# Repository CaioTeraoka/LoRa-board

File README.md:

# LoRa-board
This project is a development board that was made with the purpose of being used to create and test simples projects that contains LoRaWAN communication. Besides the LoRaWAN usage, this board also has CAN bus communication and a sensor of temperature and humidity to expand the board possibilities.

## Specifications:
**LoRa Frequency** - Only 915MHz <br>
**Power** - 5V using the USB Micro <br>
**Stackup:**
1. Signal + Components
2. Ground
3. Power
4. Ground + Components

## Main Components
- STM32F103 <br>
The STM32F103 is a series of microcontrollers developed by STMicroelectronics. It's part of the STM32 family of microcontrollers, which are based on the ARM Cortex-M processor architecture. 

- LX1276 <br>
The SX1276 is a widely known RF (Radio Frequency) transceiver module. It is a product from Semtech, a semiconductor company that specializes in wireless communication solutions. The SX1276 is part of the Semtech's LoRa (Long Range) technology family.

- SN65HVD230 <br>
The SN65HVD230 is a popular transceiver chip designed for use in Controller Area Network (CAN) bus communication systems. CAN is a widely used network protocol in automotive and industrial applications for communication between various electronic control units (ECUs) or devices. 

- AHT20 <br>
The AHT20 is a digital humidity and temperature sensor manufactured by ASAIR, a company specializing in environmental sensing solutions. The AHT20 sensor is designed to accurately measure both humidity and temperature in various applications.

## 3D Model

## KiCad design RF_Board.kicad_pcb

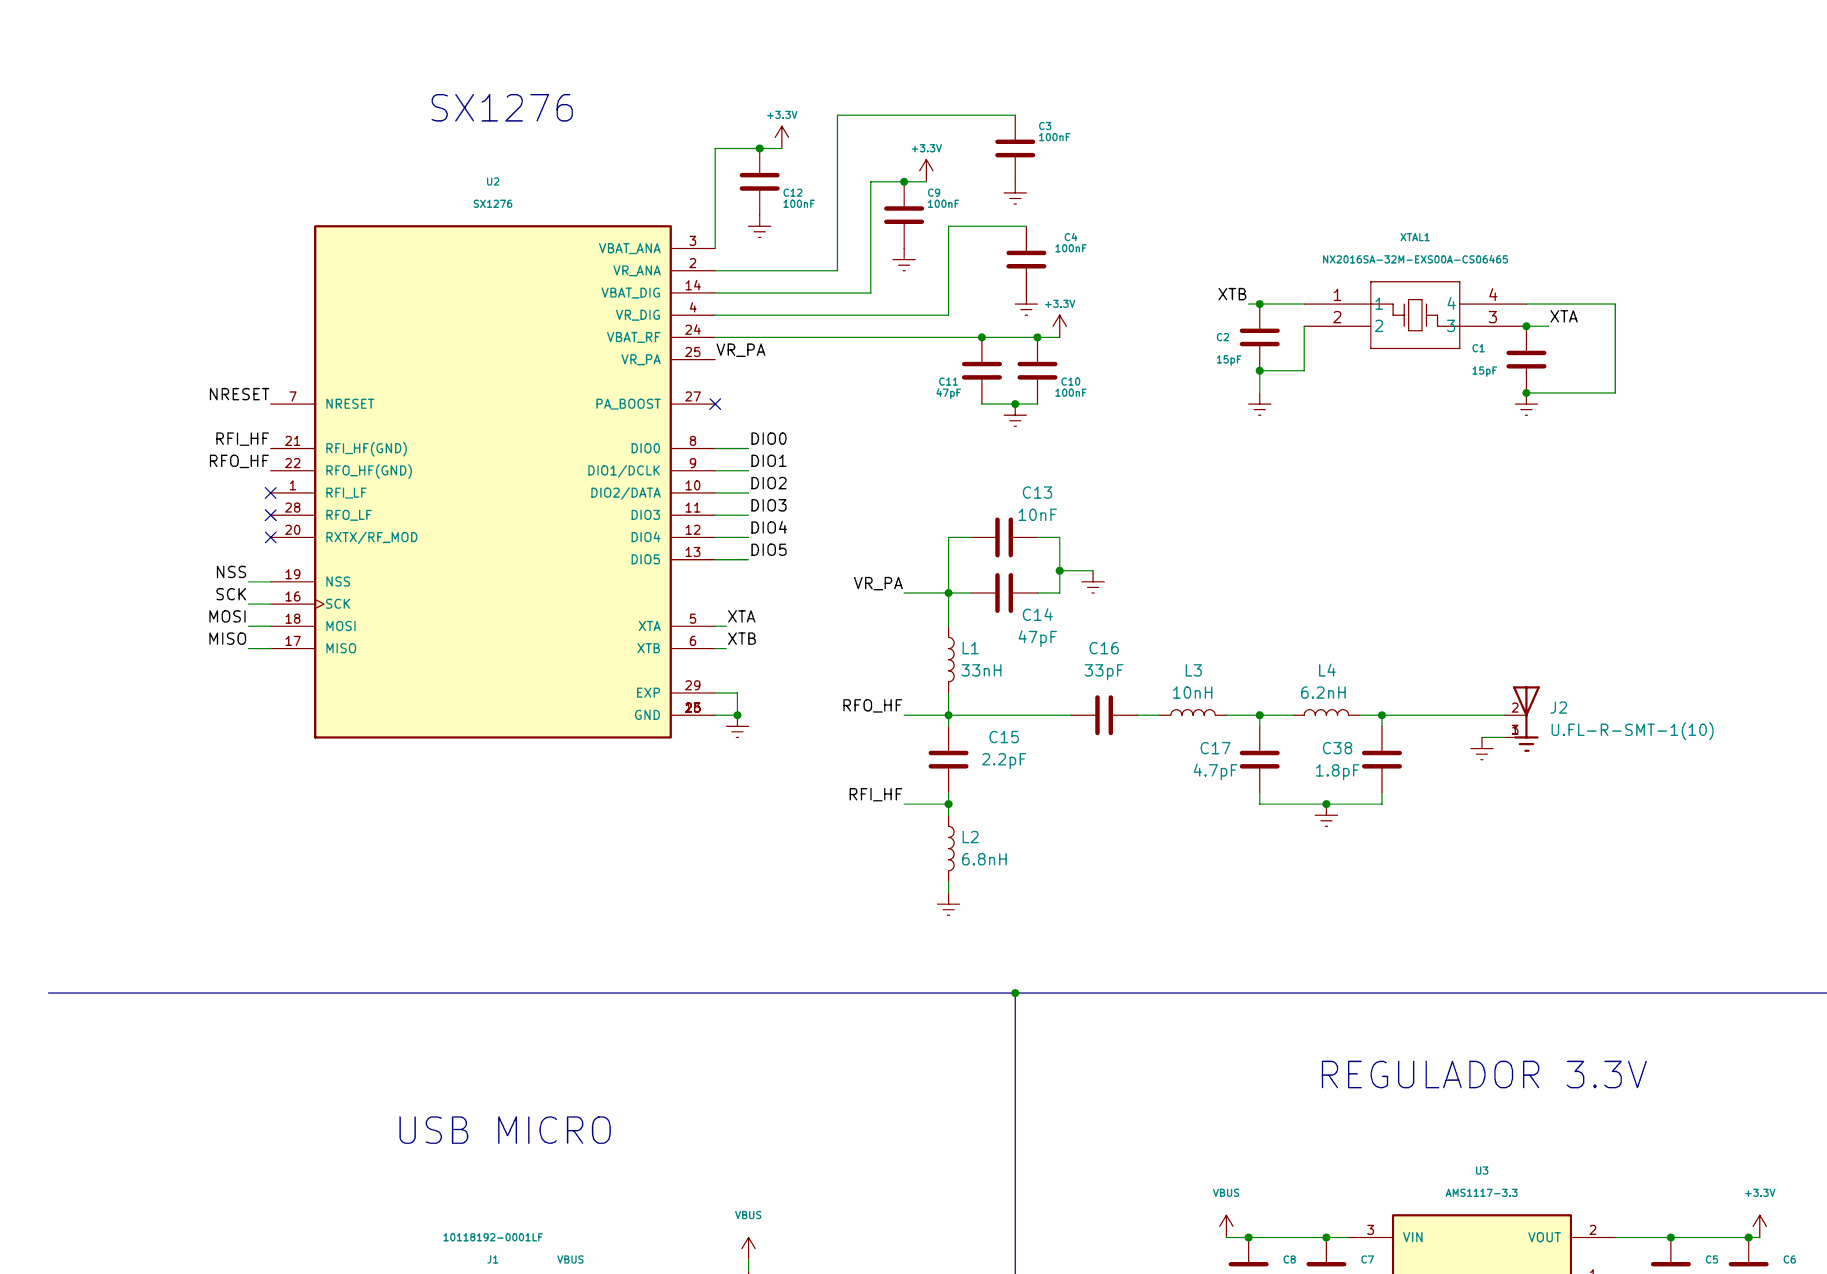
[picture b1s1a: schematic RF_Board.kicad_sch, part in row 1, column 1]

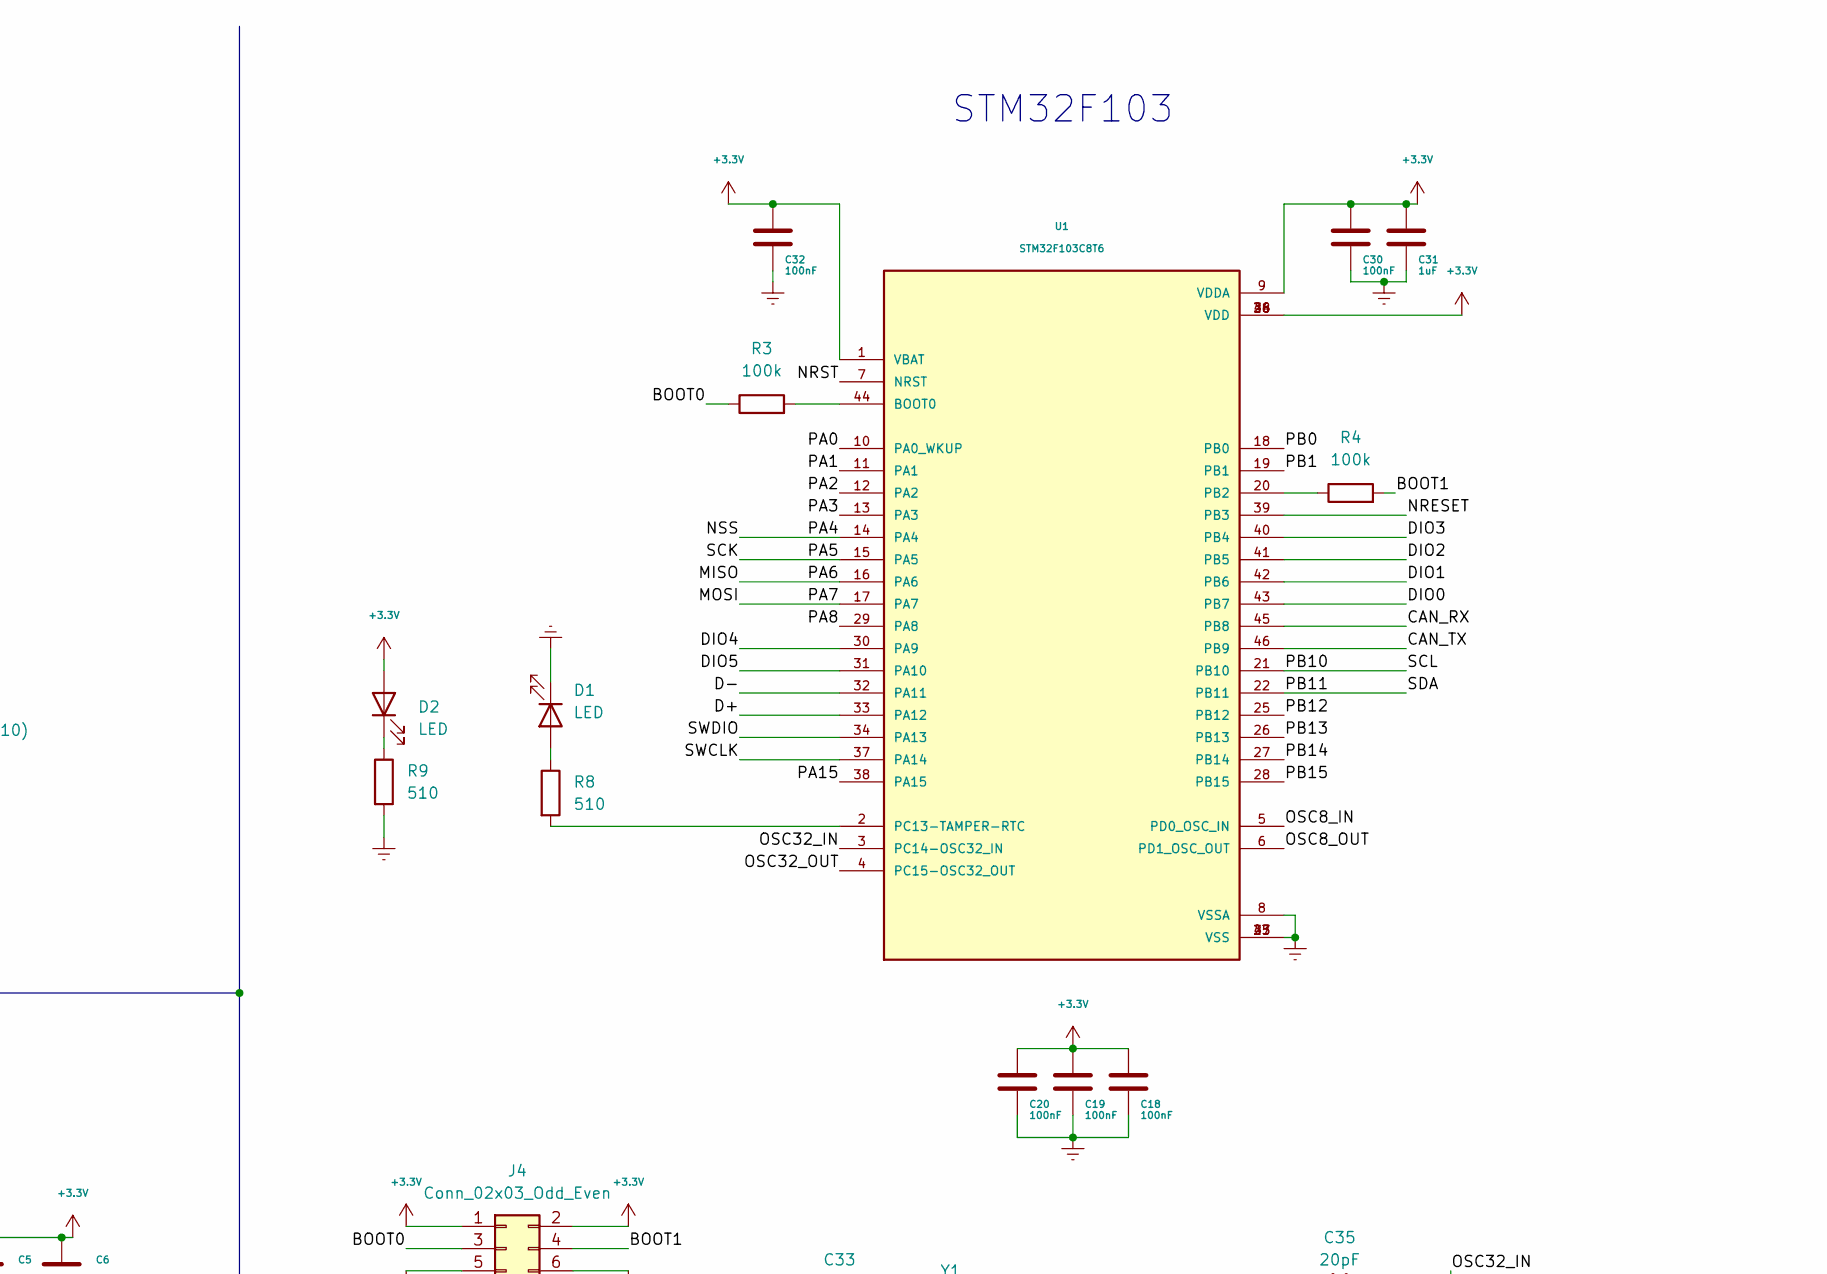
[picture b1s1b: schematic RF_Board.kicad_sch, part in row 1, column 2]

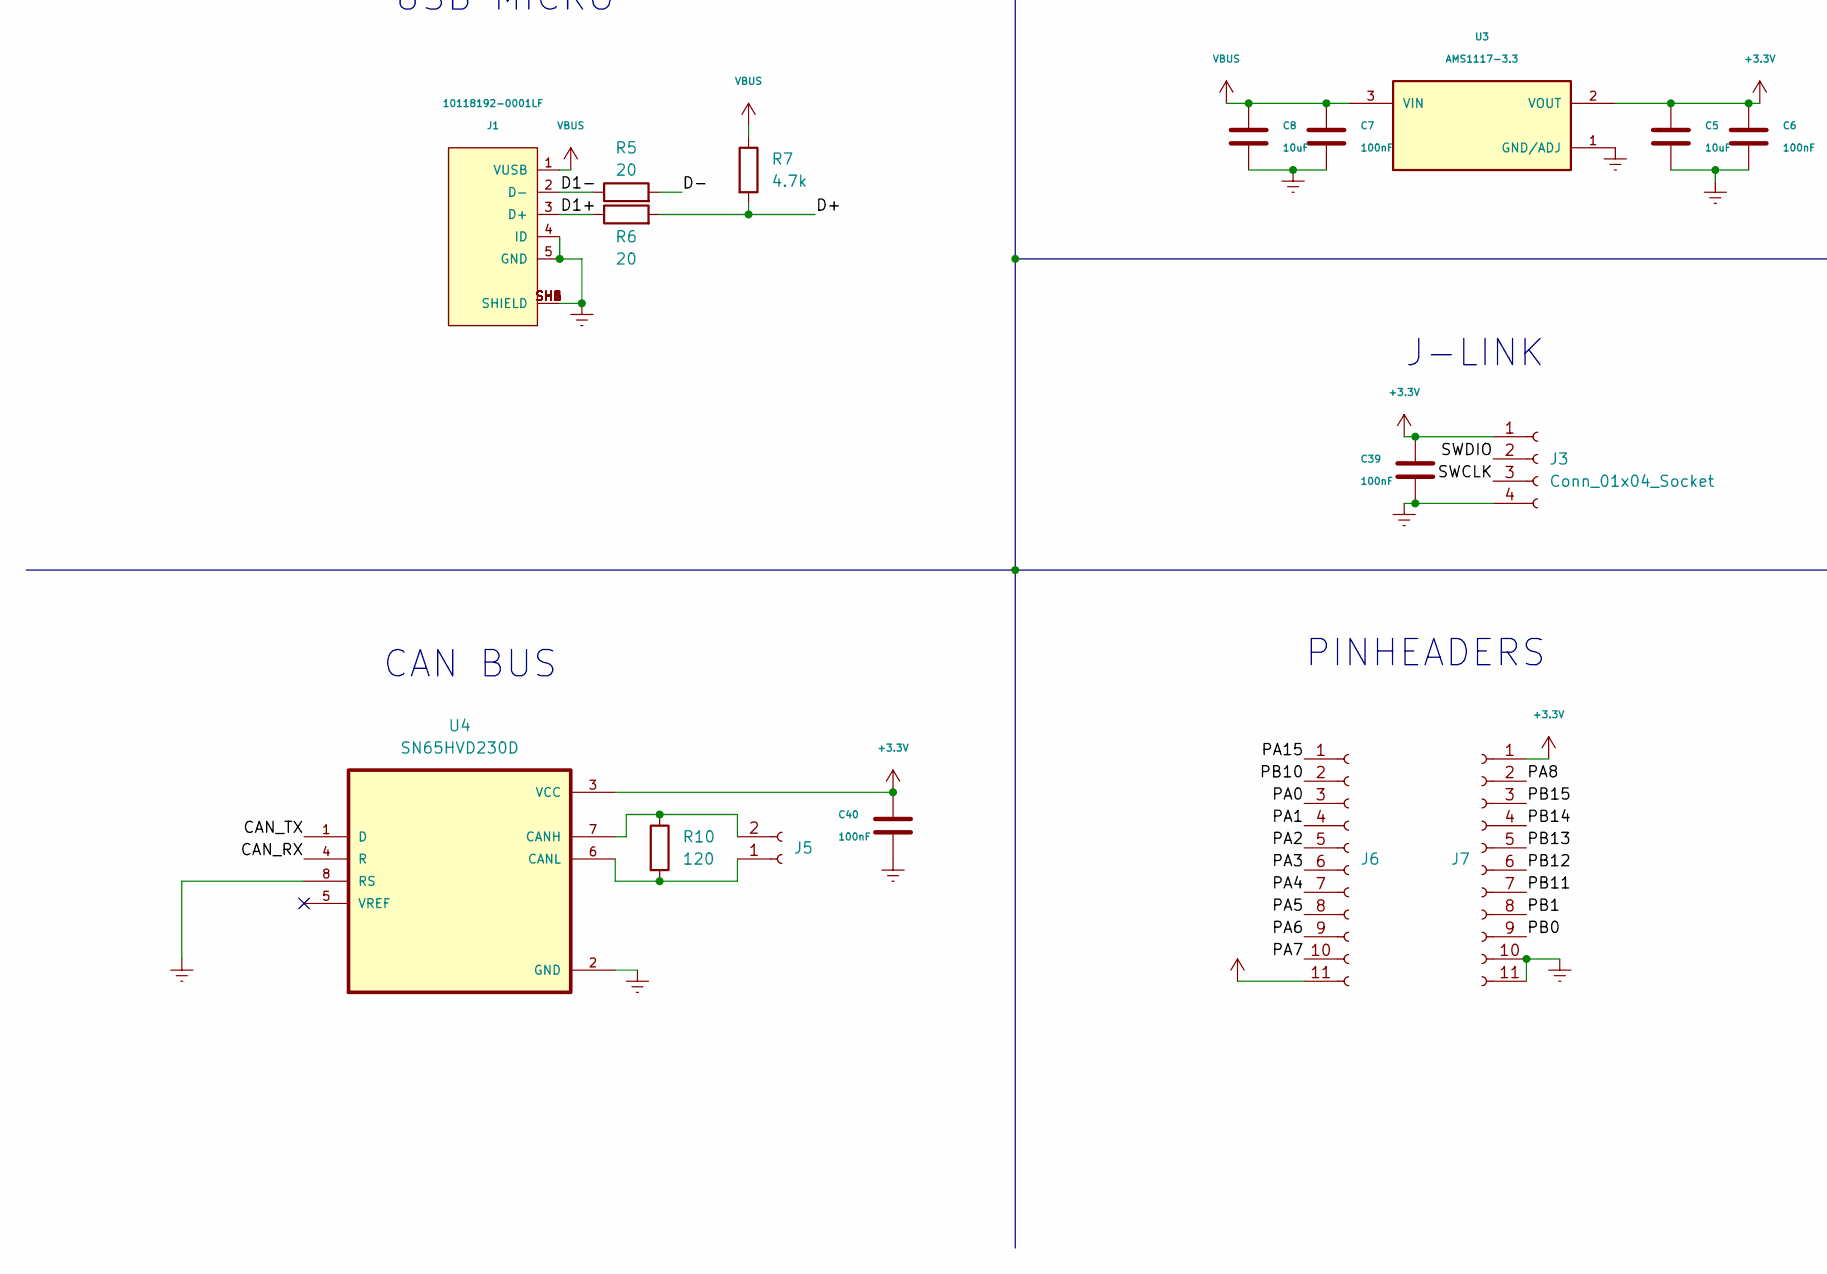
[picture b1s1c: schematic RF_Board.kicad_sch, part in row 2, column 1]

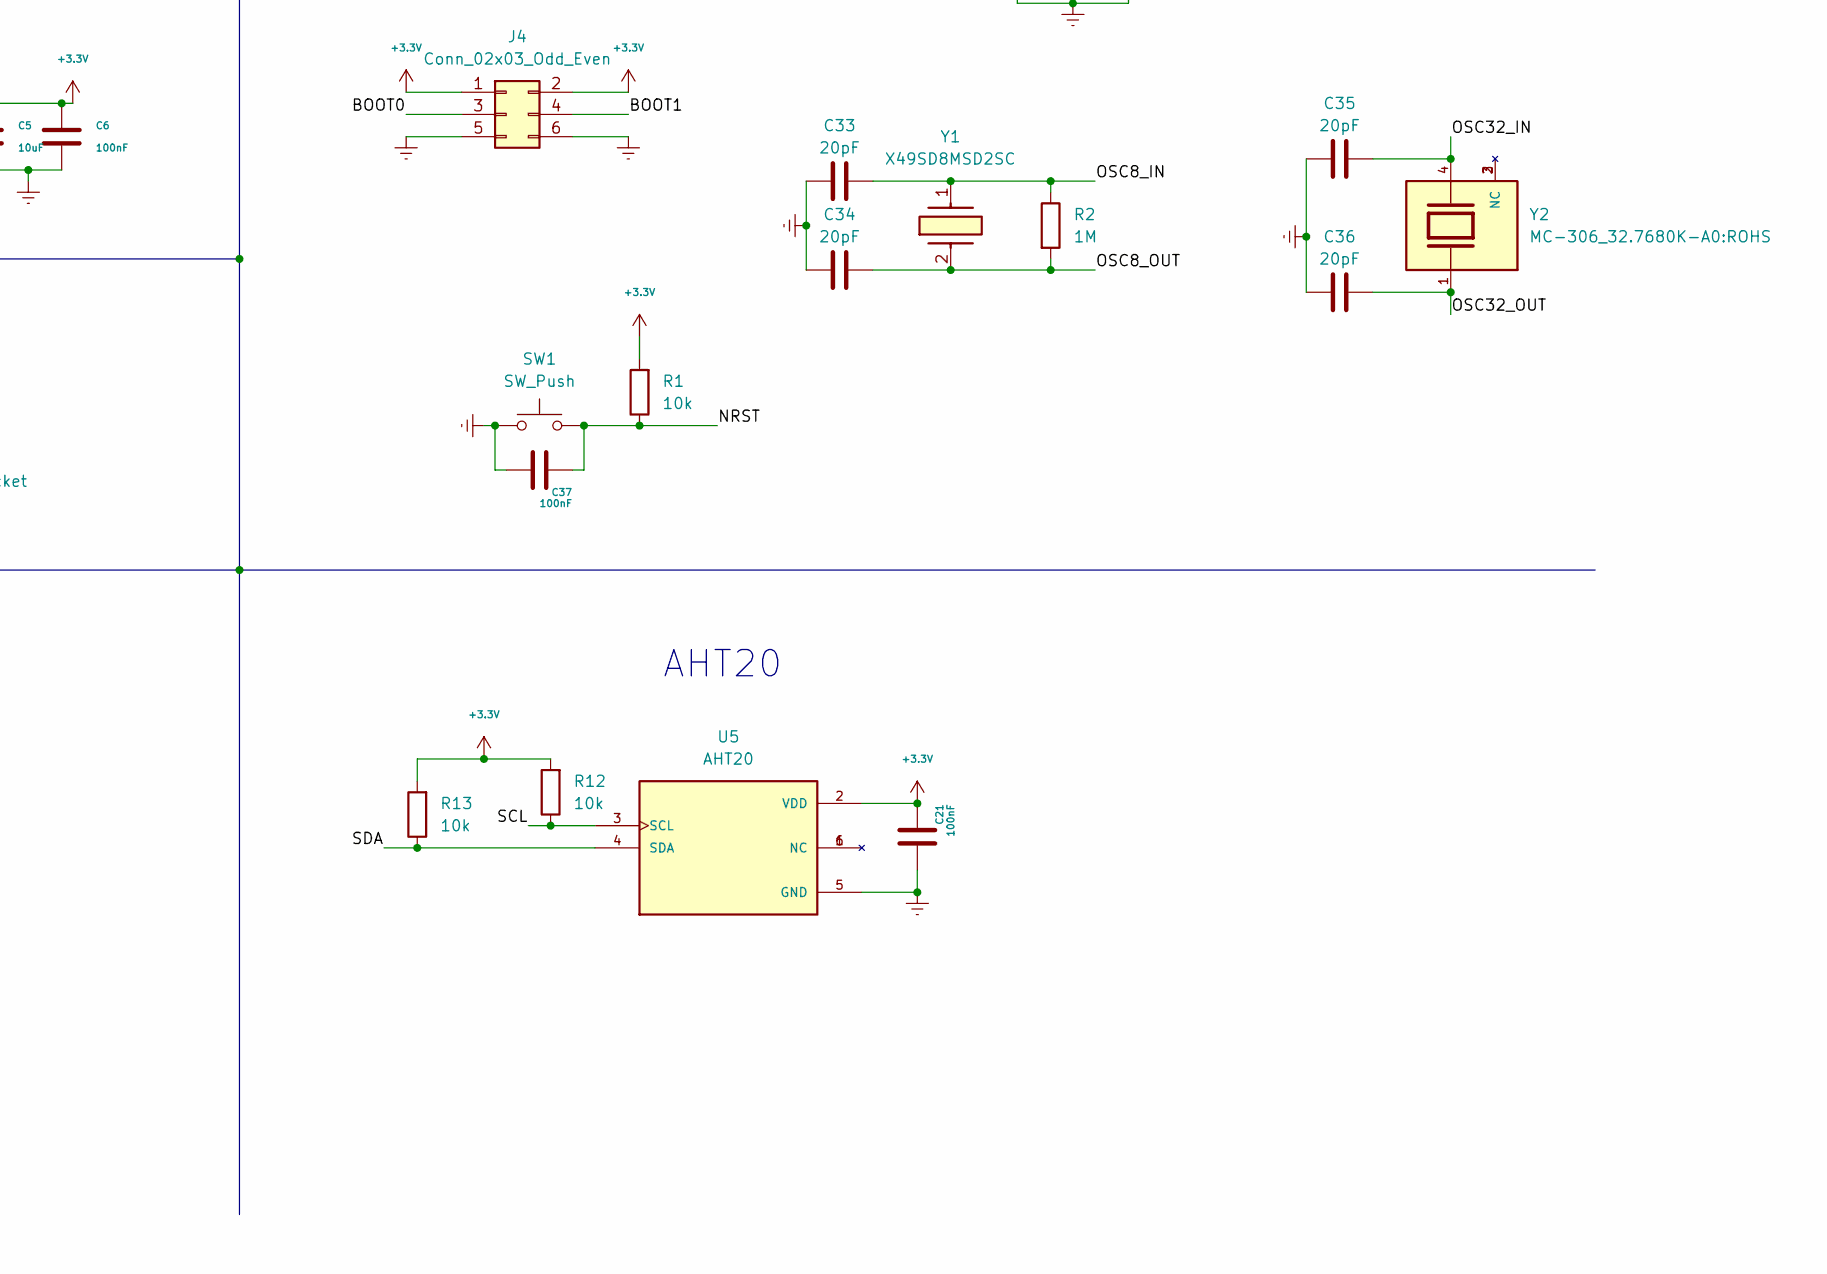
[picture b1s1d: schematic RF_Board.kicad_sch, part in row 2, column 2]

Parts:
C1, C2: 15pF; C_0402_1005Metric; LCSC PART NUMBER C2880416
C3, C4, C6, C7, C9, C10, C12, C18, C19, C20, C21, C30, C32, C37, C39, C40: 100nF; C_0402_1005Metric; LCSC PART NUMBER C163180
C5, C8: 10uF; C_0402_1005Metric; LCSC PART NUMBER C307416
C11, C14: 47pF; C_0402_1005Metric; LCSC PART NUMBER C525215
C13: 10nF; C_0402_1005Metric; LCSC PART NUMBER C466608
C15: 2.2pF; C_0402_1005Metric; LCSC PART NUMBER C123473
C16: 33pF; C_0402_1005Metric; LCSC PART NUMBER C382724
C17: 4.7pF; C_0402_1005Metric; LCSC PART NUMBER C311706
C31: 1uF; C_0402_1005Metric; LCSC PART NUMBER C162154
C33, C34, C35, C36: 20pF; C_0402_1005Metric; LCSC PART NUMBER C778217
C38: 1.8pF; C_0402_1005Metric; LCSC PART NUMBER C147346
D1, D2: LED; LED_1206_3216Metric; LCSC PART NUMBER C965822
J1: 10118192-0001LF; AMPHENOL_10118192-0001LF; PARTREV B; LCSC PART NUMBER C132564
J2: U.FL-R-SMT-1(10); HRS_U.FL-R-SMT-1(10); LCSC PART NUMBER C88374
J3: Conn_01x04_Socket; PinHeader_1x04_P2.54mm_Vertical; LCSC PART NUMBER C390680
J4: Conn_02x03_Odd_Even; PinHeader_2x03_P2.54mm_Vertical; LCSC PART NUMBER C390684
J5: Conn_01x02_Socket; PinHeader_1x02_P2.54mm_Vertical; LCSC PART NUMBER C160332
J6, J7: Conn_01x11_Socket; PinHeader_1x11_P2.54mm_Vertical; LCSC PART NUMBER C2902694
L1: 33nH; L_0402_1005Metric; LCSC PART NUMBER C2757905
L2: 6.8nH; L_0402_1005Metric; LCSC PART NUMBER C114783
L3: 10nH; L_0402_1005Metric; LCSC PART NUMBER C280981
L4: 6.2nH; L_0402_1005Metric; LCSC PART NUMBER C5137258
R1, R12, R13: 10k; R_0402_1005Metric; LCSC PART NUMBER C100196
R2: 1M; R_0402_1005Metric; LCSC PART NUMBER C323689
R3, R4: 100k; R_0402_1005Metric; LCSC PART NUMBER C431822
R5, R6: 20; R_0402_1005Metric; LCSC PART NUMBER C102873
R7: 4.7k; R_0402_1005Metric; LCSC PART NUMBER C525524
R8, R9: 510; R_0402_1005Metric; LCSC PART NUMBER C208903
R10: 120; R_0402_1005Metric; LCSC PART NUMBER C284306
SW1: SW_Push; SW_SPST_TL3342; LCSC PART NUMBER C2886894
U1: STM32F103C8T6; QFP50P900X900X160-48N; PARTREV 10; LCSC PART NUMBER C8734
U2: SX1276; QFN65P600X600X100-29N; PARTREV 6; LCSC PART NUMBER C80171
U3: AMS1117-3.3; SOT229P700X180-4N; PARTREV N/A; LCSC PART NUMBER C5199435
U4: SN65HVD230D; SOIC127P599X175-8N; LCSC PART NUMBER C12084
U5: AHT20; PSON100P300X300X110-6N; PARTREV V1.0; LCSC PART NUMBER C2757850
XTAL1: NX2016SA-32M-EXS00A-CS06465; NX2016SA_NDK; LCSC PART NUMBER C1986260
Y1: X49SD8MSD2SC; Manufacturer_Part_Number X49SD8MSD2SC; LCSC PART NUMBER C21263
Y2: MC-306_32.7680K-A0:ROHS; XTAL_MC-306_32.7680K-A0; PARTREV N/A; LCSC PART NUMBER C2650464

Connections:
+3.3V: C5.1, C6.1, C9.2, C10.2, C11.2, C12.2, C18.1, C19.1, C20.1, C21.2, C30.1, C31.1, C32.1, C39.1, C40.1, D2.2 (A), J3.1, J4.1, J4.2, J7.1, R1.2, R12.2, R13.2, U1.1 (VBAT), U1.9 (VDDA), U1.24 (VDD), U1.36 (VDD), U1.48 (VDD), U2.3 (VBAT_ANA), U2.14 (VBAT_DIG), U2.24 (VBAT_RF), U3.2 (VOUT), U4.3 (VCC), U5.2 (VDD)
/BOOT0: J4.3, R3.1
/BOOT1: J4.4, R4.2
/CAN_RX: U1.45 (PB8), U4.4 (R)
/CAN_TX: U1.46 (PB9), U4.1 (D)
/D1+: J1.3 (D+), R6.1
/D1-: J1.2 (D-), R5.1
/D+: R6.2, R7.2, U1.33 (PA12)
/D-: R5.2, U1.32 (PA11)
/DIO0: U1.43 (PB7), U2.8 (DIO0)
/DIO1: U1.42 (PB6), U2.9 (DIO1/DCLK)
/DIO2: U1.41 (PB5), U2.10 (DIO2/DATA)
/DIO3: U1.40 (PB4), U2.11 (DIO3)
/DIO4: U1.30 (PA9), U2.12 (DIO4)
/DIO5: U1.31 (PA10), U2.13 (DIO5)
/MISO: J6.9, U1.16 (PA6), U2.17 (MISO)
/MOSI: J6.10, U1.17 (PA7), U2.18 (MOSI)
/NRESET: U1.39 (PB3), U2.7 (NRESET)
/NRST: C37.2, R1.1, SW1.2, U1.7 (NRST)
/NSS: J6.7, U1.14 (PA4), U2.19 (NSS)
/OSC8_IN: C33.2, R2.1, U1.5 (PD0_OSC_IN), Y1.1
/OSC8_OUT: C34.2, R2.2, U1.6 (PD1_OSC_OUT), Y1.2 (CRYSTAL__2)
/OSC32_IN: C35.2, U1.3 (PC14-OSC32_IN), Y2.4
/OSC32_OUT: C36.2, U1.4 (PC15-OSC32_OUT), Y2.1
/PA0: J6.3, U1.10 (PA0_WKUP)
/PA1: J6.4, U1.11 (PA1)
/PA2: J6.5, U1.12 (PA2)
/PA3: J6.6, U1.13 (PA3)
/PA5: J6.8, U1.15 (PA5), U2.16 (SCK)
/PA8: J7.2, U1.29 (PA8)
/PA15: J6.1, U1.38 (PA15)
/PB0: J7.9, U1.18 (PB0)
/PB1: J7.8, U1.19 (PB1)
/PB10: J6.2, R12.1, U1.21 (PB10), U5.3 (SCL)
/PB11: J7.7, R13.1, U1.22 (PB11), U5.4 (SDA)
/PB12: J7.6, U1.25 (PB12)
/PB13: J7.5, U1.26 (PB13)
/PB14: J7.4, U1.27 (PB14)
/PB15: J7.3, U1.28 (PB15)
/RFI_HF: C15.1, L2.1, U2.21 (RFI_HF(GND))
/RFO_HF: C15.2, C16.2, L1.2, U2.22 (RFO_HF(GND))
/SWCLK: J3.3, U1.37 (PA14)
/SWDIO: J3.2, U1.34 (PA13)
/VR_PA: C13.1, C14.1, L1.1, U2.25 (VR_PA)
/XTA: C1.1, U2.5 (XTA), XTAL1.3
/XTB: C2.1, U2.6 (XTB), XTAL1.1
Earth: C1.2, C2.2, C3.1, C4.1, C5.2, C6.2, C7.2, C8.2, C9.1, C10.1, C11.1, C12.1, C13.2, C14.2, C17.2, C18.2, C19.2, C20.2, C21.1, C30.2, C31.2, C32.2, C33.1, C34.1, C35.1, C36.1, C37.1, C38.2, C39.2, C40.2, D1.1 (K), J1.4 (ID), J1.5 (GND), J1.SH1 (SHIELD), J1.SH2 (SHIELD), J1.SH3 (SHIELD), J1.SH4 (SHIELD), J1.SH5 (SHIELD), J1.SH6 (SHIELD), J2.1, J2.3, J3.4, J4.5, J4.6, J7.10, J7.11, L2.2, R9.2, SW1.1, U1.8 (VSSA), U1.23 (VSS), U1.35 (VSS), U1.47 (VSS), U2.15 (GND), U2.23 (GND), U2.26 (GND), U2.29 (EXP), U3.1 (GND/ADJ), U4.2 (GND), U4.8 (RS), U5.5 (GND), XTAL1.2, XTAL1.4
unnamed: C16.1, L3.1
unnamed: C17.1, L3.2, L4.1
unnamed: C38.1, J2.2, L4.2
unnamed: D1.2 (A), R8.1
unnamed: D2.1 (K), R9.1
unnamed: J5.1, R10.2, U4.6 (CANL)
unnamed: J5.2, R10.1, U4.7 (CANH)
unnamed: R3.2, U1.44 (BOOT0)
unnamed: R4.1, U1.20 (PB2)
unnamed: R8.2, U1.2 (PC13-TAMPER-RTC)
unnamed: C3.2, U2.2 (VR_ANA)
unnamed: C4.2, U2.4 (VR_DIG)
VBUS: C7.1, C8.1, J1.1 (VUSB), J6.11, R7.1, U3.3 (VIN)

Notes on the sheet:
USB MICRO
CAN BUS
PINHEADERS
J-LINK
SX1276
REGULADOR 3.3V
AHT20
STM32F103

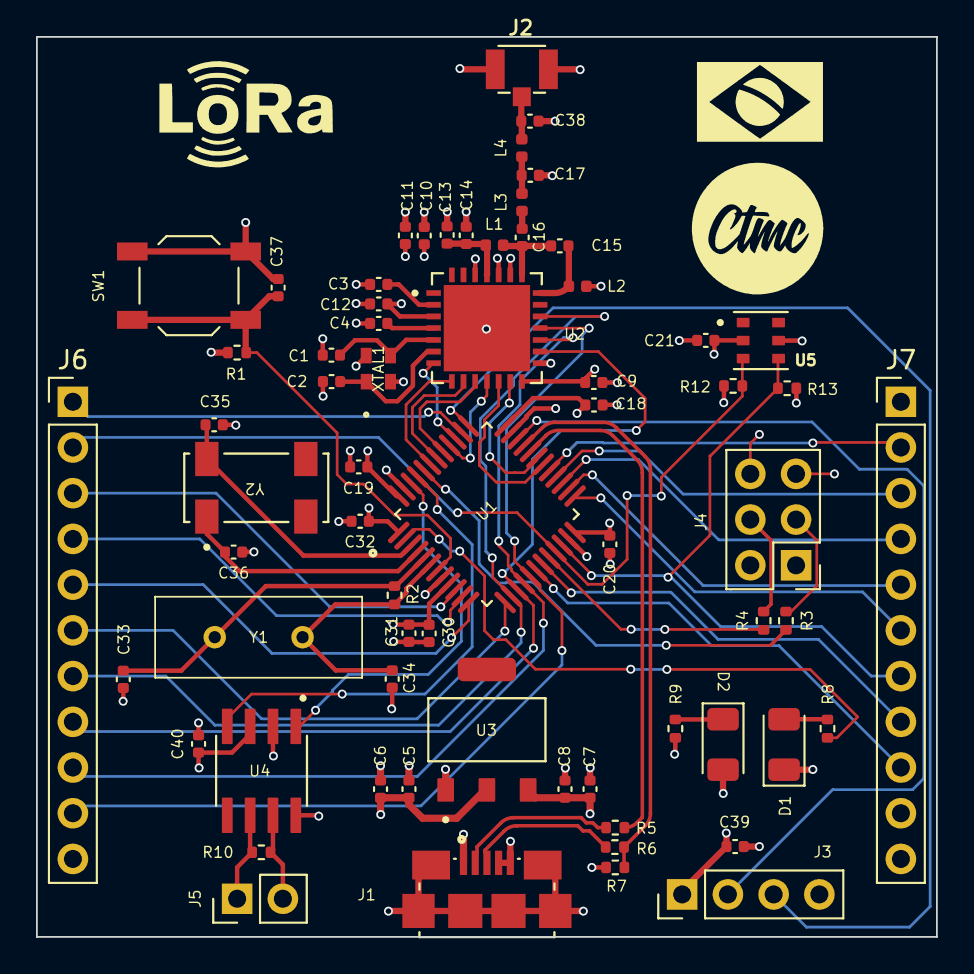
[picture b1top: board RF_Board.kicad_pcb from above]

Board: 4 copper layers, 50.0 x 50.0 mm, 66 parts (0 on the bottom side), 60 nets.

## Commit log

2023-08-23 LoRa Board V1
